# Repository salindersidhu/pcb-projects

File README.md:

# PCB-Projects

## Overview

Repository of personal PCB and electronics designs created in KiCad. Includes schematics, board layouts, revisions, and supporting documentation for various hardware projects ranging from prototypes to finalized builds. Each project is self-contained with its own custom symbols, footprints, and 3D models.

## Prerequisite Software

| Software       | Version   |
| :------------- | :-------- |
| Git            | 2.20.1+   |
| Kicad          | 10.0+     |

## Projects

### [Stereo Amplifier TDA2822](/stereo-amplifier-tda2822/)

- A compact full-range stereo amplifier PCB based on the TDA2822M audio power amplifier IC.

### [Stereo Amplifier Dual BTL TDA2822](/stereo-amplifier-dual-btl-tda2822/)

- A stereo amplifier PCB using two TDA2822M ICs in BTL configuration (one per channel) for higher output power and improved efficiency.

### [USB PD Trigger Module](/usb-pd-module/)

- A configurable USB-C Power Delivery trigger module for negotiating fixed output voltages.

### [RGB LED Dimmer](/led-dimmer/)

- A compact analog PWM LED dimmer using a 555 timer and MOSFET switching for brightness control.

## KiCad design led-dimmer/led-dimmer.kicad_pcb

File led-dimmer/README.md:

# LED Dimmer

**Rev:** 1.4

A compact analog LED dimmer PCB using a 555 timer to generate an adjustable PWM signal that drives a logic-level MOSFET for smooth LED brightness control.

## Features

- **Single-Channel PWM Control:** Adjustable LED brightness
- **PWM Generator:** NE555 timer based oscillator
- **Adjustable Brightness:** 50kΩ potentiometer
- **MOSFET Output Stage:** Logic-level N-channel MOSFET switching
- **Supply Voltage:** 12V DC input
- **LED Compatibility:** Suitable for LEDs and LED strips with appropriate current limiting
- **PCB:** Compact 2-layer layout with ground plane
- **JST XH Connectors:** 2-pin JST B2B-XH-A connectors for power input and LED output
- **Bulk Capacitance:** 470µF input capacitor for supply stabilization

## Design Overview

### PWM Generation

The circuit uses an **NE555 timer configured as an adjustable PWM oscillator**. The duty cycle is controlled using a **50kΩ potentiometer** with two steering diodes that provide separate charge and discharge paths for the timing capacitor.

This configuration provides:

- Smooth brightness adjustment
- Wide PWM duty cycle range
- Consistent LED brightness control without varying the LED supply voltage
- Simple analog control without requiring a microcontroller

### Output Stage

The PWM signal from the NE555 drives the gate of an **IRLML6344 logic-level N-channel MOSFET** through a gate resistor.

 The MOSFET operates as a **low-side switch**, connecting and disconnecting the LED load from ground according to the PWM duty cycle.

A gate pull-down resistor ensures that the MOSFET remains off when the PWM signal is not actively driving the gate.

Key characteristics:

- Low gate drive requirements
- Efficient PWM switching
- Minimal heat generation at typical LED currents
- Suitable for individual LEDs, LED strings, and low-power LED strips

### Power Input

The board operates from a **12V DC supply** connected through a **2-pin JST B2B-XH-A connector**.

A **470µF bulk capacitor** is placed across the input supply to stabilize the 12V rail and help reduce voltage transients and switching noise generated by the PWM circuit.

Additional local decoupling capacitors are used around the NE555 to improve supply stability.

Typical 12V supply sources include:

- External regulated 12V power supplies
- USB-C PD trigger modules
- DC bench supplies

### LED Output

The LED output is provided through a second **2-pin JST B2B-XH-A connector**.

The connector provides:

- **+12V supply**
- **PWM-switched low-side output**

The connected LED load is supplied directly from the 12V rail, while the MOSFET switches the return path to ground.

LEDs must include appropriate **current limiting resistors** unless the connected LED module or LED strip already incorporates its own current limiting.

## Electrical Specifications

- **Input Voltage:** 12V DC
- **PWM Channels:** 1
- **Control Method:** Analog PWM dimming
- **PWM Generator:** NE555 timer
- **Brightness Control:** 50kΩ potentiometer
- **Switching Device:** IRLML6344 logic-level N-channel MOSFET
- **Bulk Supply Capacitor:** 470µF

## Key Components

- **U1:** NE555 Timer IC (PWM generator)
- **Q1:** IRLML6344 N-channel MOSFET (LED switching)
- **R3:** 50kΩ potentiometer (PWM duty-cycle / brightness control)
- **D1–D2:** Signal diodes (PWM steering network)
- **C1:** 0.1µF timing capacitor
- **C2:** 10nF 555 control-voltage bypass capacitor
- **C3:** 470µF bulk supply capacitor
- **C4:** 0.1µF supply decoupling capacitor
- **J1:** 2-pin JST B2B-XH-A power input connector
- **J2:** 2-pin JST B2B-XH-A LED output connector

## Use Cases

- LED brightness control
- LED strip dimming
- DIY lighting projects
- Electronics learning projects involving PWM
- Integration with USB-C PD power modules
- Custom lighting for enclosures and displays
- Bench-top experimentation with analog PWM control

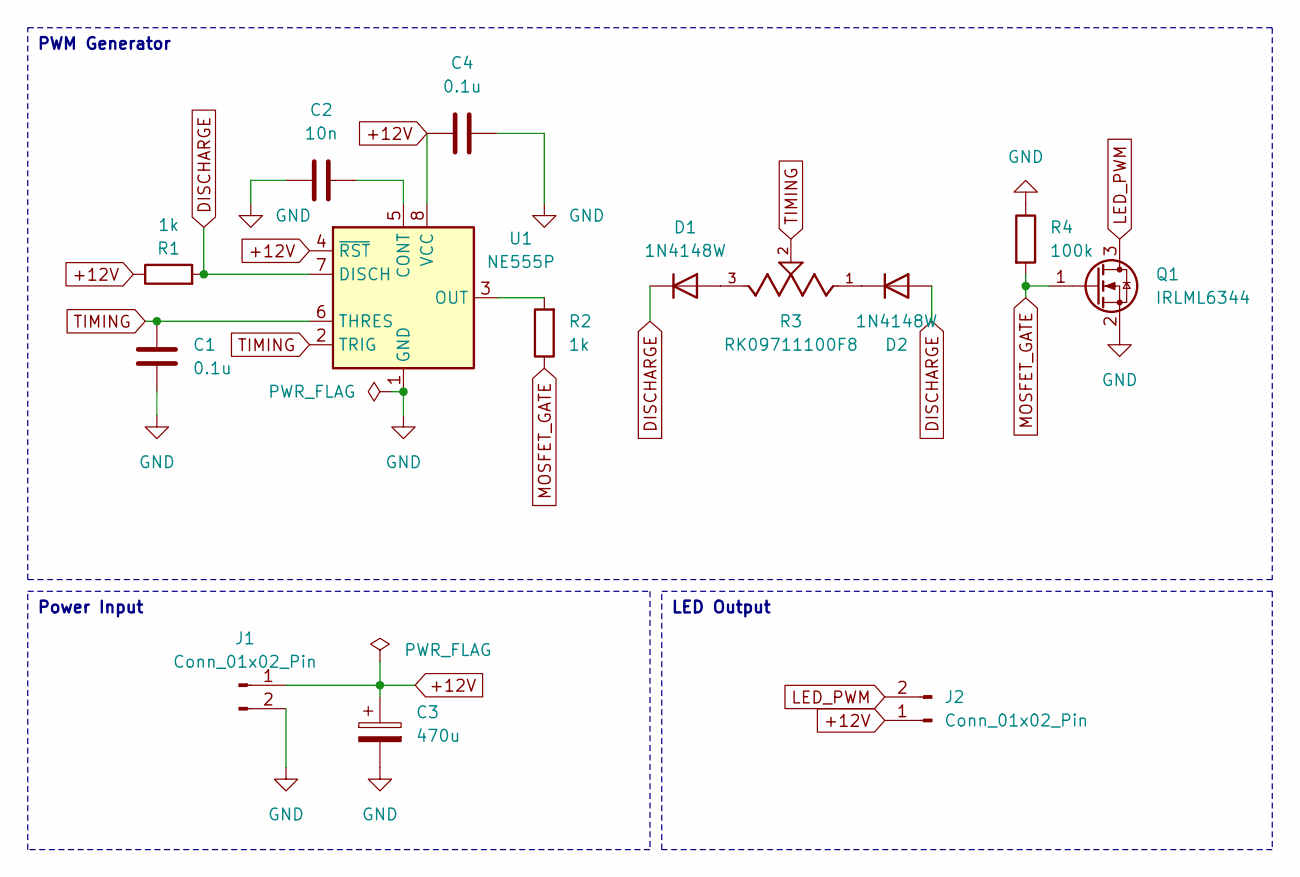
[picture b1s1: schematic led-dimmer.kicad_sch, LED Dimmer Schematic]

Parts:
C1, C4: 0.1u; C_0603_1608Metric
C2: 10n; C_0603_1608Metric
C3: 470u; CP_Radial_D6.3mm_P2.50mm
D1, D2: 1N4148W; D_SOD-123
J1, J2: Conn_01x02_Pin; JST_B2B-XH-A
Q1: IRLML6344; SOT-23
R1, R2: 1k; R_0603_1608Metric
R3: RK09711100F8; TRIM_PTN091-H50115K1A; PARTREV 1.01
R4: 100k; R_0603_1608Metric
U1: NE555P; DIP-8_W7.62mm

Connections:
+12V: C3.1, C4.1, J1.1, J2.1, R1.1, U1.4 (~RST), U1.8 (VCC)
DISCHARGE: D1.1 (K), D2.2 (A), R1.2, U1.7 (DISCH)
GND: C1.2, C2.1, C3.2, C4.2, J1.2, Q1.2 (S), R4.1, U1.1 (GND)
LED_PWM: J2.2, Q1.3 (D)
MOSFET_GATE: Q1.1 (G), R2.1, R4.2
unnamed: D1.2 (A), R3.3
unnamed: D2.1 (K), R3.1
unnamed: C2.2, U1.5 (CONT)
unnamed: R2.2, U1.3 (OUT)
TIMING: C1.1, R3.2, U1.2 (TRIG), U1.6 (THRES)

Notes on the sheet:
Power Input
PWM Generator
LED Output

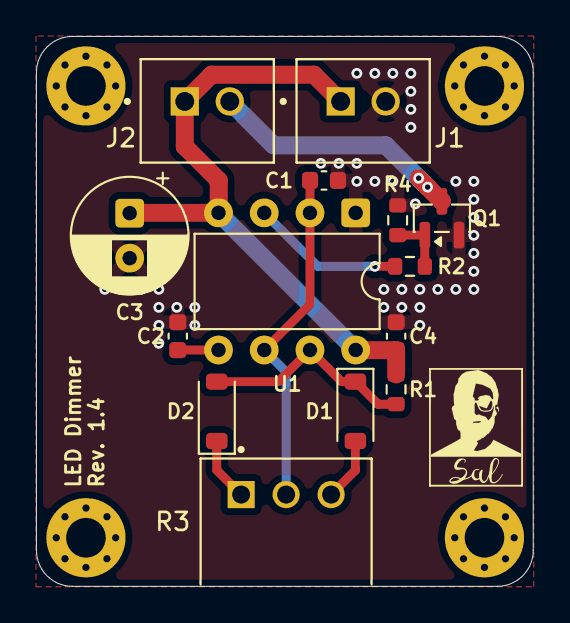
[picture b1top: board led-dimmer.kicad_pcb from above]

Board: 2 copper layers, 27.6 x 30.5 mm, 14 parts (0 on the bottom side), 10 nets.

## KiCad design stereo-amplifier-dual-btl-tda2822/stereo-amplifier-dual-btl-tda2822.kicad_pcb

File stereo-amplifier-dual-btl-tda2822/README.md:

# Stereo Amplifier Dual BTL TDA2822

**Rev:** 2.1

This project is a compact stereo audio amplifier PCB based on two TDA2822 audio power amplifier ICs. Each IC is configured in bridged-tied-load (BTL) mode to drive a single speaker, providing significantly higher output power than the standard stereo configuration. The design includes an onboard analog volume control, a standard 3.5 mm auxiliary input, and differential bridge outputs for left and right speakers.

## Features

- **Amplifier ICs:** Dual TDA2822 audio power amplifiers
- **Configuration:** Stereo (BTL mode, one IC per channel)
- **Volume Control:** 50 kΩ dual-gang potentiometer
- **Input:** 3.5 mm TRS auxiliary (line-level)
- **Output:** Differential BTL speaker outputs
- **Power Supply:** 6–15 V DC (single supply)
- **PCB:** Compact 2-layer PCB with solid ground plane
- **Mixed Technology Design:**
  - SMD resistors and ceramic capacitors
  - Through-hole electrolytic and film capacitors
- **Improved Power Filtering:**
  - 470 µF bulk reservoir capacitor per amplifier
  - Local 0.1 µF ceramic decoupling
- **Stability Features:**
  - Output Zobel networks
  - Bridge-mode compensation network
  - Input bias network
  - Local supply decoupling
- **Mounting:** Four integrated mounting holes

## Design Overview

### Power Input

- Single-supply operation (6–15 V DC recommended)
- 470 µF bulk reservoir capacitor located beside each amplifier
- 0.1 µF ceramic decoupling capacitor placed directly adjacent to each IC VCC pin
- Wide VCC routing for reduced voltage drop
- Solid ground plane with multiple stitching vias for low-impedance return paths

### Input Stage

- 3.5 mm auxiliary input (line-level)
- 4.7 µF AC coupling capacitors
- 50 kΩ dual-gang logarithmic potentiometer for volume control
- Input bias network for stable DC operating point

### Amplifier Stage

- Two TDA2822 ICs configured in bridged-tied-load (BTL) mode
- One IC dedicated to each audio channel
- 22 µF bridge coupling capacitors for improved low-frequency performance
- Local compensation network for stable bridge operation

### Output Stage

- Differential bridge outputs
- Individual Zobel network (4.7 Ω + 0.1 µF film capacitor) on each amplifier output
- Designed for 8 Ω speaker loads

> Since this is a BTL amplifier, neither speaker terminal is connected to ground. The speaker must be connected only between the two output terminals of each channel.

## PCB Layout

The PCB has been optimized for low noise and stable operation:

- Symmetrical left/right amplifier layout
- Short feedback paths
- Wide power traces
- Local decoupling located immediately adjacent to each amplifier
- Continuous ground plane
- Ground stitching vias throughout the power section
- Short differential speaker output routing

## Use Cases

- Desktop speaker amplifiers
- DIY Bluetooth speaker projects (with an external Bluetooth module)
- Retro gaming and arcade audio
- Portable speaker projects
- Educational analog electronics projects
- General-purpose stereo audio amplification

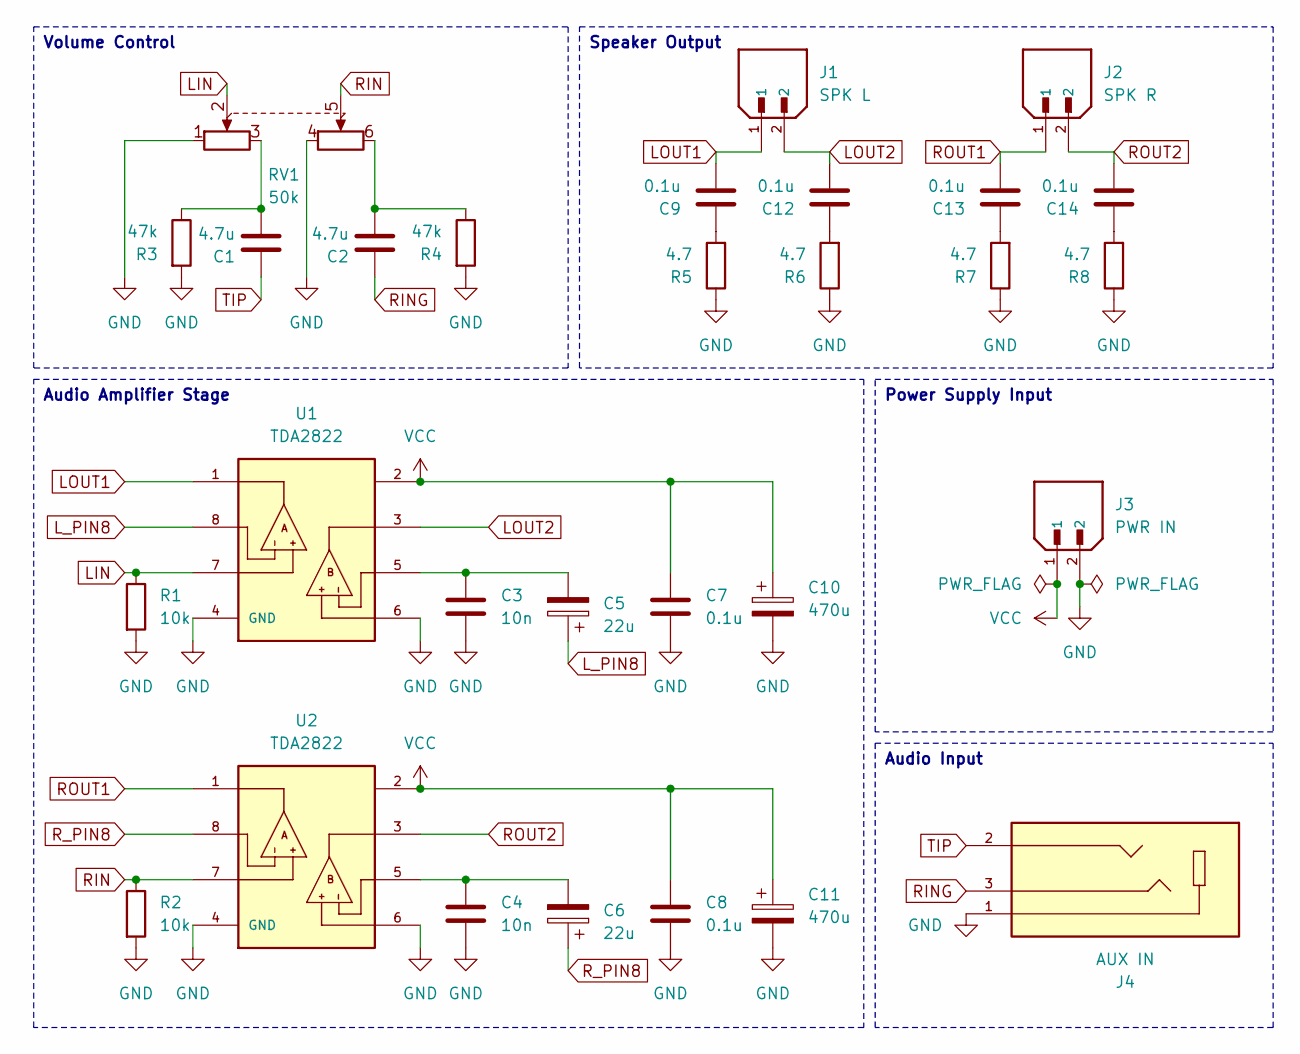
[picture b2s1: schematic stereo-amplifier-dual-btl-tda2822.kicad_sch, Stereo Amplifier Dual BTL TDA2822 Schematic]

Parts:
C1, C2: 4.7u; C_Rect_L7.2mm_W7.2mm_P5.00mm_FKS2_FKP2_MKS2_MKP2
C3, C4: 10n; C_0805_2012Metric
C5, C6: 22u; CP_Radial_D5.0mm_P2.00mm
C7, C8: 0.1u; C_0805_2012Metric
C9, C12, C13, C14: 0.1u; CAPRR500W50L730T450H950
C10, C11: 470u; CP_Radial_D8.0mm_P3.50mm
J1: SPK L; JST_B2B-XH-A; PARTREV N/A
J2: SPK R; JST_B2B-XH-A; PARTREV N/A
J3: PWR IN; JST_B2B-XH-A; PARTREV N/A
J4: AUX IN; CUI_SJ1-3513N; PARTREV 1.02
R1, R2: 10k; R_0805_2012Metric_Pad1.20x1.40mm_HandSolder
R3, R4: 47k; R_0805_2012Metric_Pad1.20x1.40mm_HandSolder
R5, R6, R7, R8: 4.7; R_1206_3216Metric_Pad1.30x1.75mm_HandSolder
RV1: 50k; Potentiometer_Alps_RK163_Dual_Horizontal
U1, U2: TDA2822; DIP762W45P254L1092H508Q8; PARTREV September 2003

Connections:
GND: C3.1, C4.1, C7.1, C8.1, C10.2, C11.2, J3.2, J4.1, R1.2, R2.2, R3.2, R4.2, R5.1, R6.1, R7.1, R8.1, RV1.1, RV1.4, U1.4 (GND_4), U1.6, U2.4 (GND_4), U2.6
LIN: R1.1, RV1.2, U1.7
LOUT1: C9.2, J1.1, U1.1
LOUT2: C12.2, J1.2, U1.3
L_PIN8: C5.1, U1.8
unnamed: C1.2, R3.1, RV1.3
unnamed: C2.2, R4.1, RV1.6
unnamed: C3.2, C5.2, U1.5
unnamed: C4.2, C6.2, U2.5
unnamed: C9.1, R5.2
unnamed: C12.1, R6.2
unnamed: C13.1, R7.2
unnamed: C14.1, R8.2
RIN: R2.1, RV1.5, U2.7
RING: C2.1, J4.3
ROUT1: C13.2, J2.1, U2.1
ROUT2: C14.2, J2.2, U2.3
R_PIN8: C6.1, U2.8
TIP: C1.1, J4.2
VCC: C7.2, C8.2, C10.1, C11.1, J3.1, U1.2, U2.2

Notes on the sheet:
Power Supply Input
Speaker Output
Audio Input
Audio Amplifier Stage
Volume Control

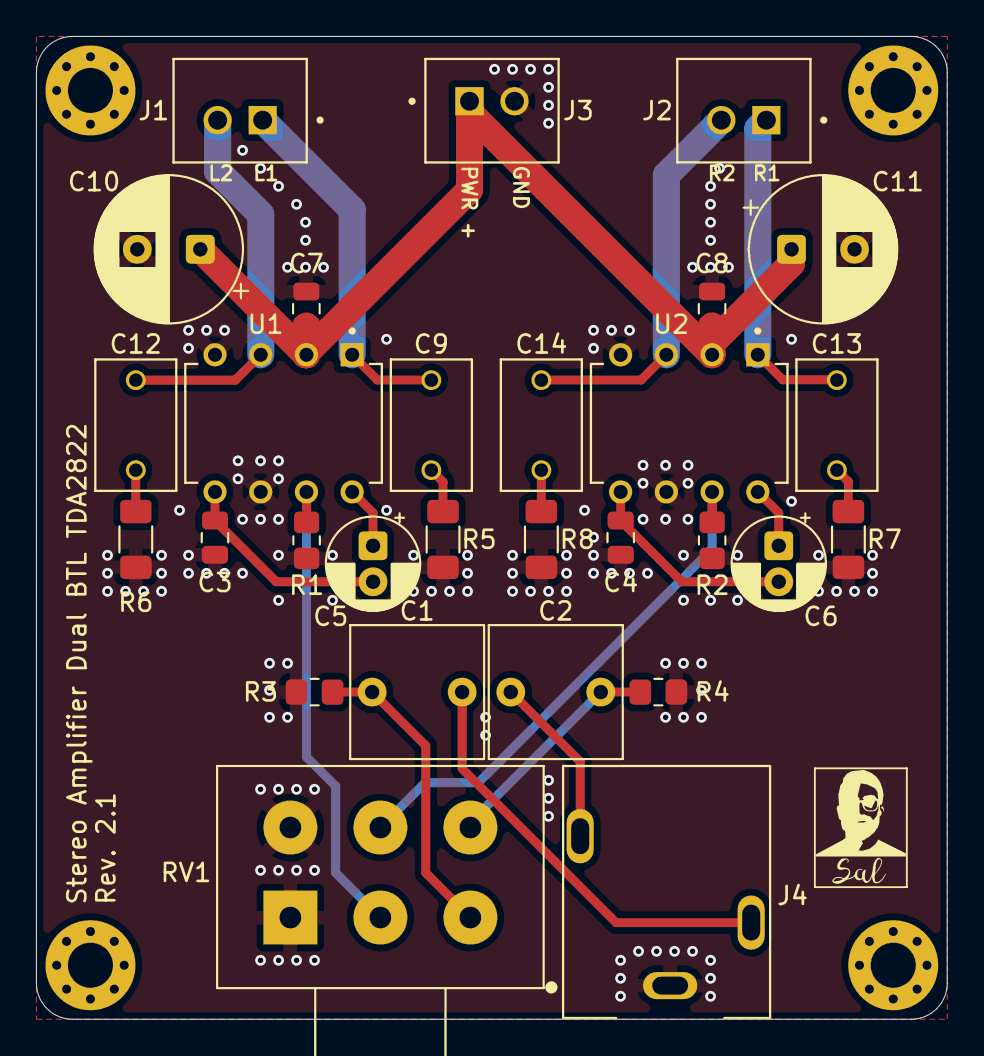
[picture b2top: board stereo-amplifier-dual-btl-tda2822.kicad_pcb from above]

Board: 2 copper layers, 50.6 x 54.6 mm, 29 parts (0 on the bottom side), 20 nets.

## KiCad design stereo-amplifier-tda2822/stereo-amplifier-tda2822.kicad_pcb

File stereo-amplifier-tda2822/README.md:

# Stereo Amplifier TDA2822

**Rev:** 3.0

This project is a compact stereo audio amplifier PCB based on the TDA2822 audio power amplifier IC. The amplifier is configured in the standard stereo (single-ended) configuration, providing clean, low-noise audio for small speakers. The design includes an onboard analog volume control, a standard 3.5 mm auxiliary input, and AC-coupled speaker outputs suitable for general-purpose audio applications.

## Features

- **Amplifier IC:** Single TDA2822 dual-channel audio power amplifier
- **Configuration:** Stereo (single-ended mode)
- **Volume Control:** 50 kΩ dual-gang potentiometer
- **Input:** 3.5 mm TRS auxiliary (line-level)
- **Output:** AC-coupled stereo speaker outputs
- **Power Supply:** 6–15 V DC (single supply)
- **PCB:** Compact 2-layer PCB with solid ground plane
- **Through-Hole Design:**
  - Through-hole resistors and capacitors
- **Power Filtering:**
  - 470 µF bulk supply capacitor
  - Local 0.1 µF ceramic decoupling
- **Stability Features:**
  - Output Zobel networks
  - Input bias network
  - Local supply decoupling
- **Mounting:** Four integrated mounting holes

## Design Overview

### Power Input

- Single-supply operation (6–15 V DC recommended)
- 470 µF bulk reservoir capacitor for supply filtering
- 0.1 µF ceramic decoupling capacitor located directly adjacent to the TDA2822 VCC pin
- Wide power routing with a continuous ground plane for low-impedance current return

### Input Stage

- Standard 3.5 mm stereo auxiliary input
- 2.2 µF AC coupling capacitors on both channels
- 50 kΩ dual-gang potentiometer providing analog volume adjustment
- 47 kΩ input pulldown resistors to establish a stable input reference
- 18 kΩ input bias resistors at the amplifier inputs

### Amplifier Stage

- Single TDA2822 configured in standard stereo (single-ended) mode
- Independent left and right amplifier channels
- 100 µF feedback capacitors providing AC gain stabilization and improved low-frequency response
- Local supply decoupling positioned adjacent to the IC to reduce supply noise

### Output Stage

- 2200 µF output coupling capacitors for DC isolation
- Individual Zobel network (4.7 Ω resistor + 0.1 µF capacitor) on each output for amplifier stability
- Designed for 8 Ω speaker loads

## PCB Layout

The PCB has been arranged to minimize noise while maintaining a compact footprint:

- Symmetrical left/right channel layout
- Short routing between the amplifier outputs and output capacitors
- Local decoupling positioned immediately beside the amplifier supply pin
- Continuous ground plane for low-impedance return paths
- Ground stitching vias throughout the power section
- Separation of input and output routing to reduce unwanted coupling
- Wide power traces for improved current handling

## Use Cases

- Desktop stereo speakers
- DIY Bluetooth speaker projects (with an external Bluetooth receiver)
- Educational analog electronics projects
- Portable audio projects
- Small multimedia speaker systems
- General-purpose stereo audio amplification

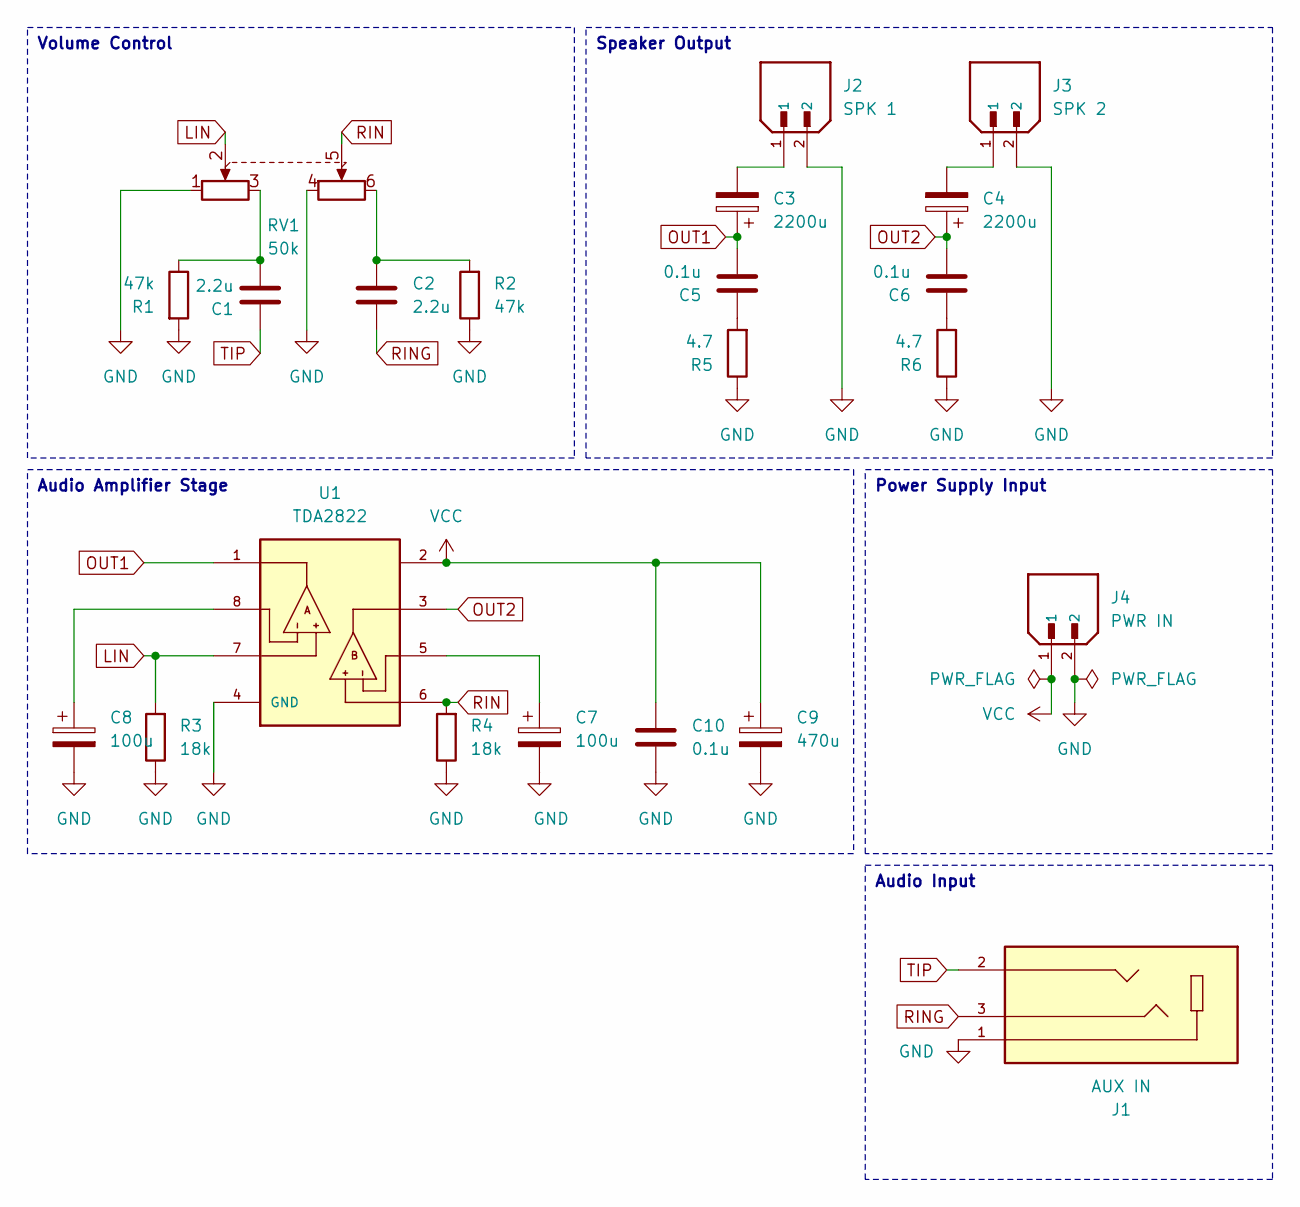
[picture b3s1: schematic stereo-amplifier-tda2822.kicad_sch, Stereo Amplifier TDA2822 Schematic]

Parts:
C1, C2: 2.2u; C_Rect_L7.2mm_W7.2mm_P5.00mm_FKS2_FKP2_MKS2_MKP2
C3, C4: 2200u; CP_Radial_D10.0mm_P5.00mm
C5, C6, C10: 0.1u; CAPRR500W50L730T450H950
C7, C8: 100u; CP_Radial_D5.0mm_P2.50mm
C9: 470u; CP_Radial_D6.3mm_P2.50mm
J1: AUX IN; CUI_SJ1-3513N; PARTREV 1.02
J2: SPK 1; JST_B2B-XH-A; PARTREV N/A
J3: SPK 2; JST_B2B-XH-A; PARTREV N/A
J4: PWR IN; JST_B2B-XH-A; PARTREV N/A
R1, R2: 47k; R_Axial_DIN0207_L6.3mm_D2.5mm_P10.16mm_Horizontal
R3, R4: 18k; R_Axial_DIN0207_L6.3mm_D2.5mm_P10.16mm_Horizontal
R5, R6: 4.7; R_Axial_DIN0207_L6.3mm_D2.5mm_P10.16mm_Horizontal
RV1: 50k; Potentiometer_Alps_RK163_Dual_Horizontal
U1: TDA2822; DIP762W45P254L1092H508Q8; PARTREV September 2003

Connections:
GND: C7.2, C8.2, C9.2, C10.1, J1.1, J2.2, J3.2, J4.2, R1.2, R2.1, R3.1, R4.1, R5.1, R6.1, RV1.1, RV1.4, U1.4 (GND_4)
LIN: R3.2, RV1.2, U1.7
unnamed: C1.2, R1.1, RV1.3
unnamed: C2.1, R2.2, RV1.6
unnamed: C3.2, J2.1
unnamed: C4.2, J3.1
unnamed: C5.1, R5.2
unnamed: C6.1, R6.2
unnamed: C7.1, U1.5
unnamed: C8.1, U1.8
OUT1: C3.1, C5.2, U1.1
OUT2: C4.1, C6.2, U1.3
RIN: R4.2, RV1.5, U1.6
RING: C2.2, J1.3
TIP: C1.1, J1.2
VCC: C9.1, C10.2, J4.1, U1.2

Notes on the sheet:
Power Supply Input
Audio Input
Audio Amplifier Stage
Volume Control
Speaker Output

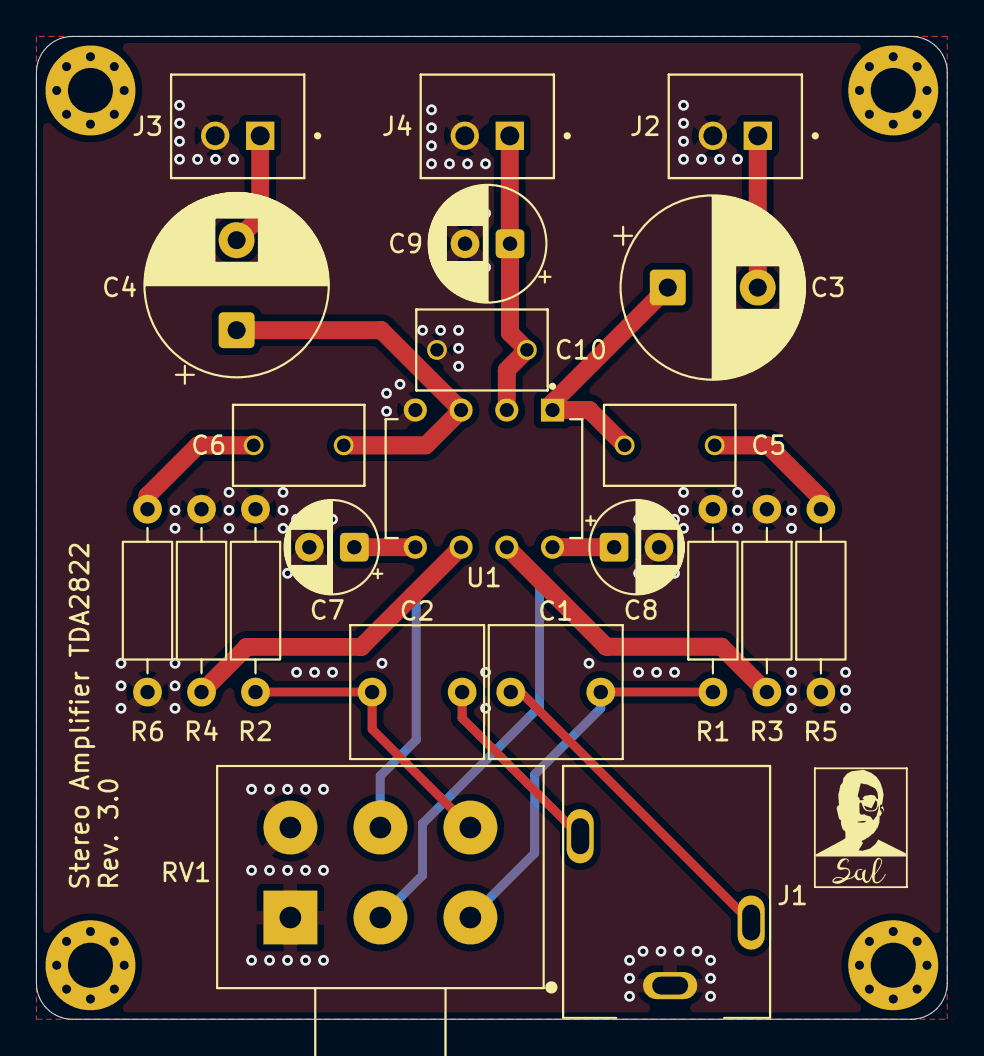
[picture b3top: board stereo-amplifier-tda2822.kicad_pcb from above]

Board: 2 copper layers, 50.6 x 54.6 mm, 22 parts (0 on the bottom side), 16 nets.

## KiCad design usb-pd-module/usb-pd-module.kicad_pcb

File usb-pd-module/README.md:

# USB PD Module

**Rev:** 4.7

A compact, configurable USB-C Power Delivery trigger module based on the CH221K, designed for safe and reliable voltage PD negotiation with a simple and robust power output.

## Features
- USB-C Power Delivery trigger based on CH221K
- Negotiates fixed PD voltages: 5V / 9V / 12V / 15V / 20V
- 5-position DIP switch voltage selection
- RGB LED status indicator:
  - **Red:** Standard 5V (no PD negotiation)
  - **Purple:** PD negotiated voltage active
- Large bulk output capacitor (4700 µF)
- Output bleed resistor for faster discharge
- Compact 2-layer PCB
- Mounting holes for enclosure integration

## Design Overview

### Simplified Power Path

The output is directly driven by the negotiated voltage from the CH221K, ensuring consistent and reliable operation across all supported voltage levels.

### Status Indication

An RGB LED is used to indicate power state:

- **Red:** Default USB 5V (no PD contract established)  
- **Purple:** Successful PD negotiation (selected voltage active)

This provides immediate visual feedback.

### PD Configuration

Voltage selection is handled with a resistor ladder and DIP switch connected to the CH221K configuration input.

### Signal Integrity

- Short, symmetric CC1/CC2 routing  
- ESD protection on CC lines  
- Local decoupling at the PD controller  
- Solid ground plane with stitched returns  

## Electrical Specifications

- **Input:** USB-C PD source  
- **Negotiated Output Voltages:** 5V, 9V, 12V, 15V, 20V  
- **Max Output Current:** Limited by USB-C source  
- **Output Capacitance:** 4700 µF bulk  

## Key Components

- **U1:** CH221K USB-C PD controller  
- **C1:** 4700 µF bulk output capacitor  
- **USB-C Connector:** 6-pin USB-C receptacle  
- **U2:** SPX1117M3 LDO regulator  
- **LED:** RGB LED for status indication

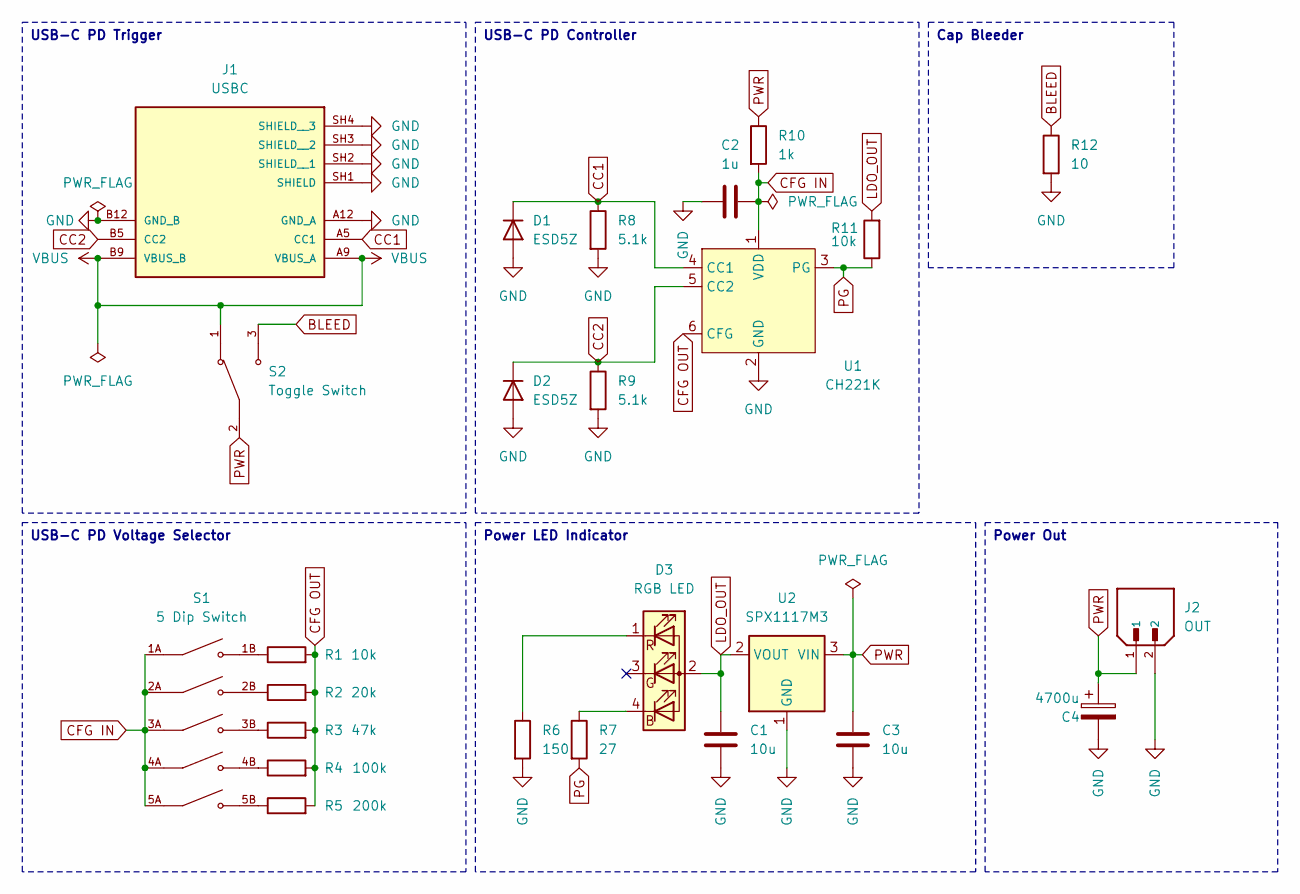
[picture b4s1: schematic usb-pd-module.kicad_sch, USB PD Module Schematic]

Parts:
C1, C3: 10u; C_0603_1608Metric
C2: 1u; C_0603_1608Metric
C4: 4700u; CP_Radial_D16.0mm_P7.50mm
D1, D2: ESD5Z; D_SOD-523
D3: RGB LED; LED_D5.0mm-4_RGB
J1: USBC; AMPHENOL_10164359-00011LF; PARTREV A
J2: OUT; JST_B2B-XH-A; PARTREV N/A
R1, R11: 10k; R_0603_1608Metric_Pad0.98x0.95mm_HandSolder
R2: 20k; R_0603_1608Metric_Pad0.98x0.95mm_HandSolder
R3: 47k; R_0603_1608Metric_Pad0.98x0.95mm_HandSolder
R4: 100k; R_0603_1608Metric_Pad0.98x0.95mm_HandSolder
R5: 200k; R_0603_1608Metric_Pad0.98x0.95mm_HandSolder
R6: 150; R_0603_1608Metric_Pad0.98x0.95mm_HandSolder
R7: 27; R_0603_1608Metric_Pad0.98x0.95mm_HandSolder
R8, R9: 5.1k; R_0603_1608Metric_Pad0.98x0.95mm_HandSolder
R10: 1k; R_0603_1608Metric_Pad0.98x0.95mm_HandSolder
R12: 10; R_2512_6332Metric
S1: 5 Dip Switch; SW_DS04-254-1L-05BK; PARTREV V0.0
S2: Toggle Switch; SW_100SP1T2B4M7QE; PARTREV E
U1: CH221K; SOT-23-6
U2: SPX1117M3; SOT-223-3_TabPin2

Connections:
BLEED: R12.1, S2.3
CC1: D1.1 (K), J1.A5 (CC1), R8.1, U1.4 (CC1)
CC2: D2.1 (K), J1.B5 (CC2), R9.1, U1.5 (CC2)
CFG IN: C2.1, R10.2, S1.1A, S1.2A, S1.3A, S1.4A, S1.5A, U1.1 (VDD)
CFG OUT: R1.2, R2.2, R3.2, R4.2, R5.2, U1.6 (CFG)
GND: C1.1, C2.2, C3.1, C4.2, D1.2 (A), D2.2 (A), J1.A12 (GND_A), J1.B12 (GND_B), J1.SH1 (SHIELD), J1.SH2 (SHIELD__1), J1.SH3 (SHIELD__2), J1.SH4 (SHIELD__3), J2.2, R6.2, R8.2, R9.2, R12.2, U1.2 (GND), U2.1 (GND)
LDO_OUT: C1.2, D3.2 (A), R11.2, U2.2 (VOUT)
unnamed: D3.4 (BK), R7.1
unnamed: D3.1 (RK), R6.1
unnamed: R1.1, S1.1B
unnamed: R2.1, S1.2B
unnamed: R3.1, S1.3B
unnamed: R4.1, S1.4B
unnamed: R5.1, S1.5B
PG: R7.2, R11.1, U1.3 (PG)
PWR: C3.2, C4.1, J2.1, R10.1, S2.2, U2.3 (VIN)
VBUS: J1.A9 (VBUS_A), J1.B9 (VBUS_B), S2.1

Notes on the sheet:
USB-C PD Voltage Selector
USB-C PD Controller
USB-C PD Trigger
Power LED Indicator
Power Out
Cap Bleeder

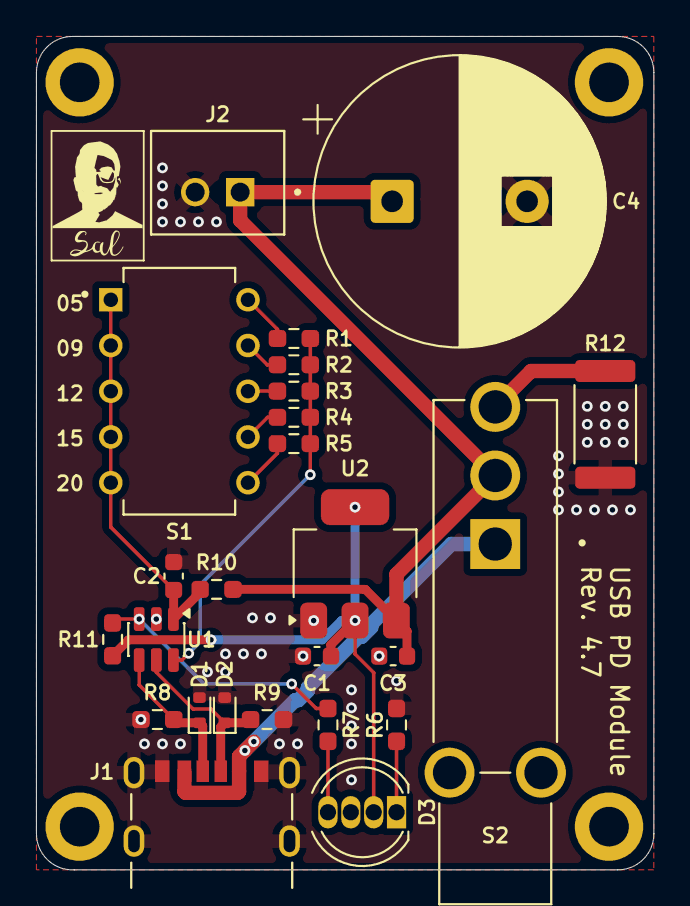
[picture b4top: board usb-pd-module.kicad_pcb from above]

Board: 2 copper layers, 34.3 x 46.3 mm, 25 parts (0 on the bottom side), 17 nets.

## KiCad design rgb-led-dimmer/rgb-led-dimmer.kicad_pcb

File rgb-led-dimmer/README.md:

# RGB LED Dimmer

**Rev:** 1.0

A compact analog RGB LED dimmer PCB using independent PWM control for each color channel. The design uses three 555 timer circuits to generate adjustable PWM signals that drive MOSFET switches for smooth brightness control of RGB LEDs.

## Features

- **Independent RGB control:** Three separate PWM dimmer channels
- **PWM Generator:** 555 timer based oscillator per color channel
- **Adjustable Brightness:** 50kΩ potentiometer per channel
- **MOSFET Output Stage:** Logic-level N-channel MOSFET switching
- **Supply Voltage:** 12V DC input
- **LED Compatibility:** Designed for standard 5mm RGB LEDs with current-limiting resistors
- **PCB:** Compact 2-layer layout with ground plane
- **Output Connector:** Dedicated RGB LED output header
- **Modular Power Input:** Designed to pair with external regulated power modules

## Design Overview

### PWM Generation

Each color channel uses a dedicated **555 timer configured as an adjustable PWM oscillator**. The duty cycle is controlled using a 50kΩ potentiometer with steering diodes that allow independent control of charge and discharge paths.

This configuration provides:

- Smooth brightness adjustment  
- Wide PWM duty cycle range  
- Consistent LED brightness control without changing LED current  

### Output Stage

Each PWM signal drives the gate of a **logic-level N-channel MOSFET** through a gate resistor.

The MOSFET operates as a **low-side switch**, allowing efficient PWM dimming of the LED channels.

Key characteristics:

- Low gate drive requirements
- Minimal heat generation at typical LED currents
- Suitable for multiple LEDs per channel

### Power Input

The board operates from a **12V DC supply**.

A local **bulk capacitor** stabilizes the supply rail and reduces switching noise generated by the PWM dimming circuits.

Typical supply sources include:

- External 12V power supplies
- USB-C PD trigger modules
- DC bench supplies

### LED Output

The RGB LED output header provides connections for:

- **Red channel**
- **Green channel**
- **Blue channel**
- **Common supply rail**

Each LED must include its own **current-limiting resistor** to ensure safe operation.

## Electrical Specifications

- **Input Voltage:** 12V DC  
- **PWM Channels:** 3 (Red, Green, Blue)  
- **Control Method:** Analog PWM dimming  
- **Typical Load:** Up to 4 standard RGB LEDs per channel (with resistors)  
- **Switching Devices:** Logic-level MOSFETs  

## Key Components

- **U1–U3:** 555 Timer ICs (PWM generators)  
- **Q1–Q3:** IRLML6344 N-channel MOSFETs (LED switching)  
- **VR1–VR3:** 50kΩ potentiometers (brightness control)  
- **D1–D6:** Signal diodes (PWM steering network)  
- **C10:** Bulk supply capacitor  
- **J1:** RGB LED output connector  
- **J2:** Power input connector  

## Use Cases

- RGB LED accent lighting  
- DIY lighting controllers  
- Electronics learning projects involving PWM  
- Integration with USB-C PD power modules  
- Custom lighting for enclosures and displays

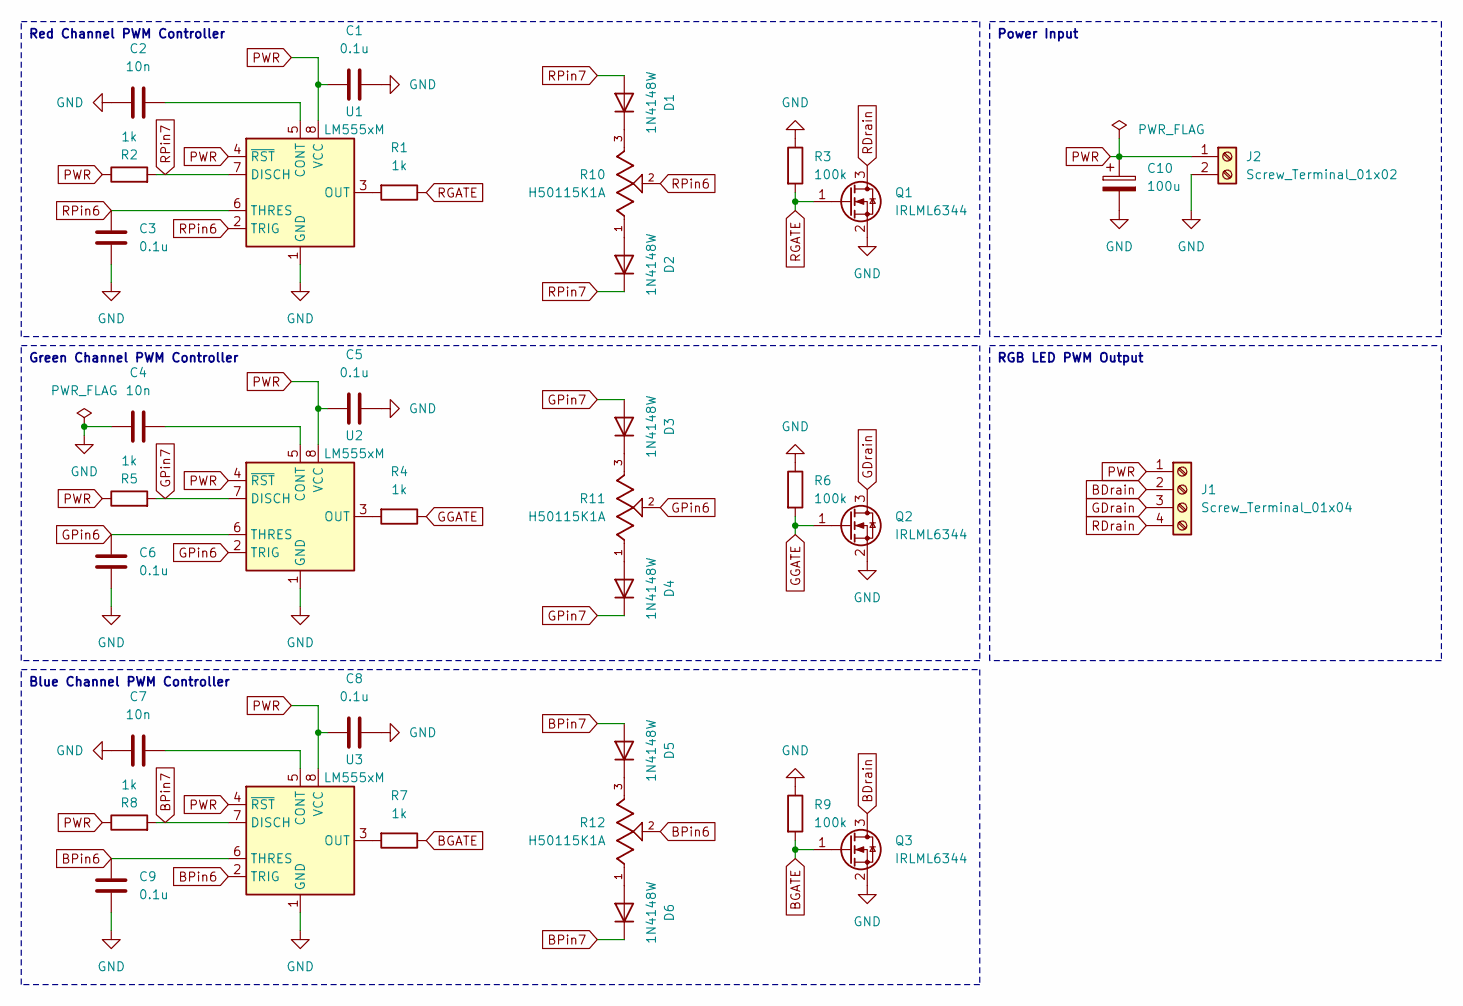
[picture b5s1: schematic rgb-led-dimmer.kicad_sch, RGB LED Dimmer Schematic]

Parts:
C1, C3, C5, C6, C8, C9: 0.1u; C_0603_1608Metric
C2, C4, C7: 10n; C_0603_1608Metric
C10: 100u; CP_Radial_D5.0mm_P2.50mm
D1, D2, D3, D4, D5, D6: 1N4148W; D_SOD-123
J1: Screw_Terminal_01x04; TerminalBlock_MaiXu_MX126-5.0-04P_1x04_P5.00mm
J2: Screw_Terminal_01x02; TerminalBlock_MaiXu_MX126-5.0-02P_1x02_P5.00mm
Q1, Q2, Q3: IRLML6344; SOT-23
R1, R2, R4, R5, R7, R8: 1k; R_0603_1608Metric
R3, R6, R9: 100k; R_0603_1608Metric
R10, R11, R12: H50115K1A; TRIM_PTN091-H50115K1A; PARTREV 1.01
U1, U2, U3: LM555xM; SOIC-8_3.9x4.9mm_P1.27mm

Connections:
BDrain: J1.2, Q3.3 (D)
BGATE: Q3.1 (G), R7.1, R9.2
BPin6: C9.1, R12.2, U3.2 (TRIG), U3.6 (THRES)
BPin7: D5.2 (A), D6.1 (K), R8.2, U3.7 (DISCH)
GDrain: J1.3, Q2.3 (D)
GGATE: Q2.1 (G), R4.1, R6.2
GND: C1.2, C2.1, C3.2, C4.2, C5.2, C6.2, C7.2, C8.2, C9.2, C10.2, J2.2, Q1.2 (S), Q2.2 (S), Q3.2 (S), R3.1, R6.1, R9.1, U1.1 (GND), U2.1 (GND), U3.1 (GND)
GPin6: C6.1, R11.2, U2.2 (TRIG), U2.6 (THRES)
GPin7: D3.2 (A), D4.1 (K), R5.2, U2.7 (DISCH)
unnamed: D1.1 (K), R10.3
unnamed: D2.2 (A), R10.1
unnamed: D3.1 (K), R11.3
unnamed: D4.2 (A), R11.1
unnamed: D5.1 (K), R12.3
unnamed: D6.2 (A), R12.1
unnamed: C2.2, U1.5 (CONT)
unnamed: R1.2, U1.3 (OUT)
unnamed: C4.1, U2.5 (CONT)
unnamed: R4.2, U2.3 (OUT)
unnamed: C7.1, U3.5 (CONT)
unnamed: R7.2, U3.3 (OUT)
PWR: C1.1, C5.1, C8.1, C10.1, J1.1, J2.1, R2.1, R5.1, R8.1, U1.4 (~RST), U1.8 (VCC), U2.4 (~RST), U2.8 (VCC), U3.4 (~RST), U3.8 (VCC)
RDrain: J1.4, Q1.3 (D)
RGATE: Q1.1 (G), R1.1, R3.2
RPin6: C3.1, R10.2, U1.2 (TRIG), U1.6 (THRES)
RPin7: D1.2 (A), D2.1 (K), R2.2, U1.7 (DISCH)

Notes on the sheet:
Power Input
RGB LED PWM Output
Red Channel PWM Controller
Blue Channel PWM Controller
Green Channel PWM Controller

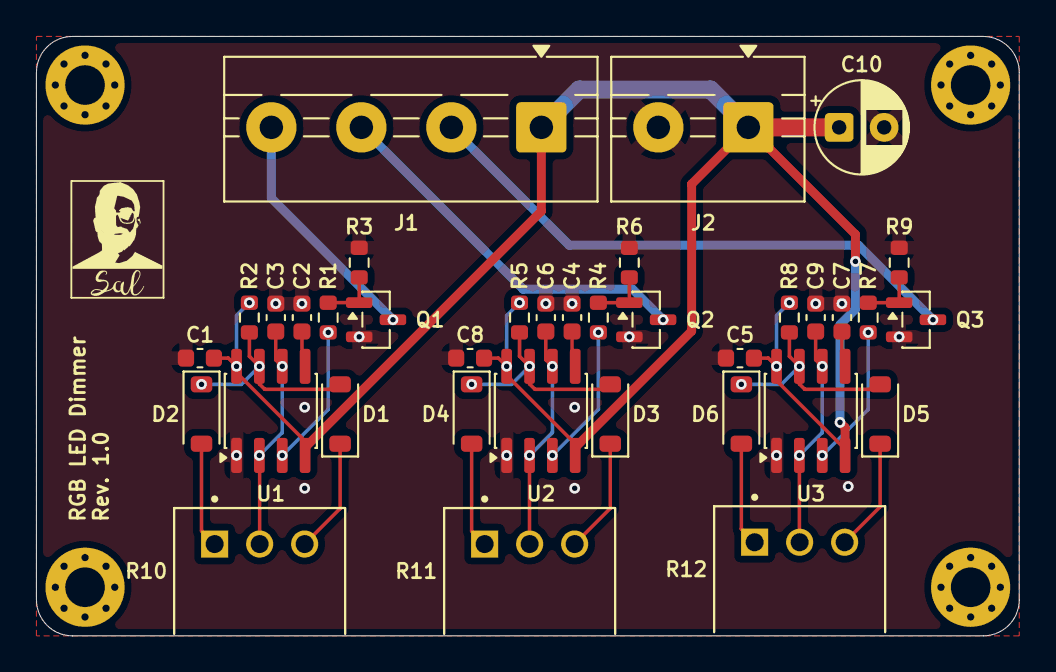
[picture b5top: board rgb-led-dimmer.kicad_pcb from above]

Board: 2 copper layers, 54.6 x 33.3 mm, 36 parts (0 on the bottom side), 26 nets.

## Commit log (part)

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2026-02-21 Update README and LICENSE with project details and licensing information
2026-02-21 Updated .gitignore
2026-02-21 Add complete stereo amp PCB project with schematics, PCB, 3D models, and README
2026-02-21 Removed glb
2026-02-21 Add complete USB PD Module project with schematics, PCB, 3d gif and README
2026-02-22 Updated READMEs for stero-speaker-amp and usb-pd-module projects
2026-02-22 Update usb-pd-module project
2026-03-12 Add complete RGB LED Dimmer project with schematics, PCB, 3d gif and README
2026-03-12 Removed duplicate RGB LED Dimmer kicad schematic
2026-03-12 Fix gif link in the RGB LED Dimmer README
2026-03-21 Update USB PD Module to Rev 4.5 with improved power path and RGB LED indicator
2026-04-19 Migrate usb-pd-module to KiCad 10 and add self-contained symbol, footprint, and 3D model libraries
2026-04-19 Migrate stereo-speaker-amp to KiCad 10 and add self-contained symbol, footprint, and 3D model libraries
2026-04-19 Migrate rgb-led-dimmer to KiCad 10 and add self-contained symbol, footprint, and 3D model libraries
2026-04-19 Update README with KiCad 10.0+ requirement and self-contained project note
2026-05-28 Adjust USB-C connector and main switch placement for better enclosure compatibility
2026-06-27 Redesign LED dimmer as single-channel PWM module
2026-06-27 Fixed led dimmer gif link in README
2026-06-28 Update LED Dimmer PCB

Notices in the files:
README.md:
License: Apache
